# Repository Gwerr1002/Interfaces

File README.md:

## Interfases Programables

Proyectos del curso de Interfases Programables en lenguaje Micropython (ESP32).

## Temas
- Programación orientada a objetos y Estructuras de datos.
- Comunicación serie
- Interrupciones
- Eventos asíncronos
- Comunicación i2C y SPI
  - Acelerómetro MPU6050
  - Oxímetro MAX30102
  - Pantalla OLED SSD1306
- Comunicación Bluetooth
- IoT

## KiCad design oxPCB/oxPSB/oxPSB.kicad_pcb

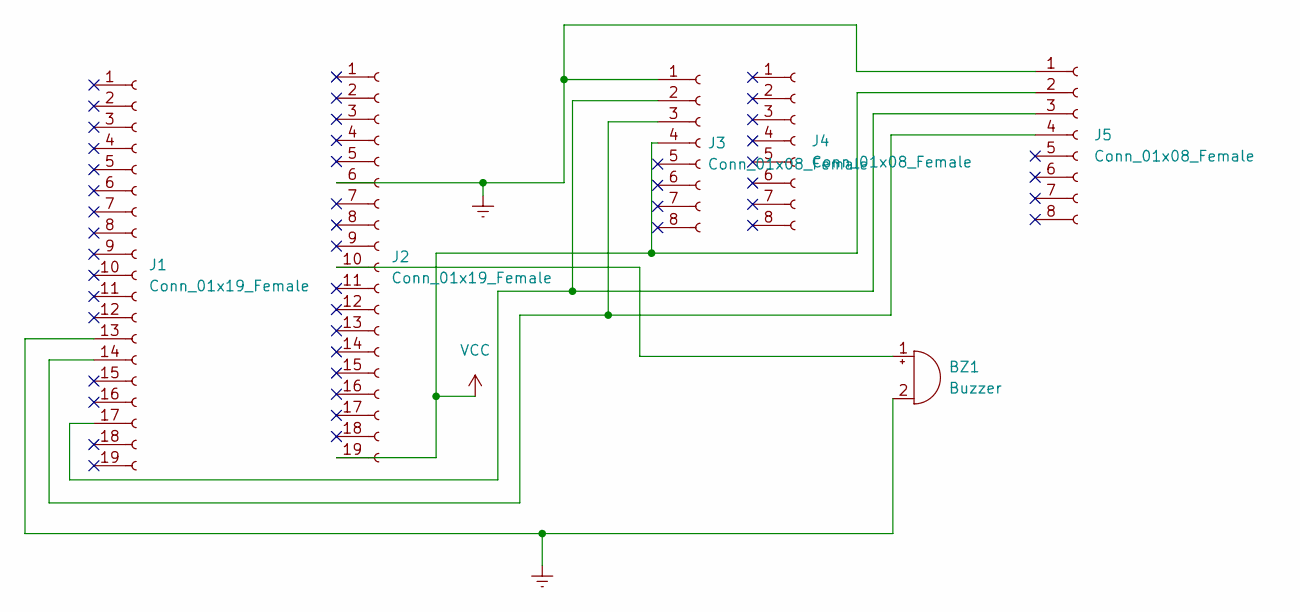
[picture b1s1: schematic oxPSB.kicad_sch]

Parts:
BZ1: Buzzer
J1: Conn_01x19_Female
J2: Conn_01x19_Female; PinHeader_1x19_P2.54mm_Vertical
J3, J5: Conn_01x08_Female; PinHeader_1x08_P2.54mm_Vertical
J4: Conn_01x08_Female

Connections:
Earth: BZ1.2 (+), J1.13, J2.6, J3.1, J5.1
unnamed: BZ1.1 (-), J2.10
unnamed: J1.14, J3.3, J5.4
unnamed: J1.17, J3.2, J5.3
VCC: J2.19, J3.4, J5.2

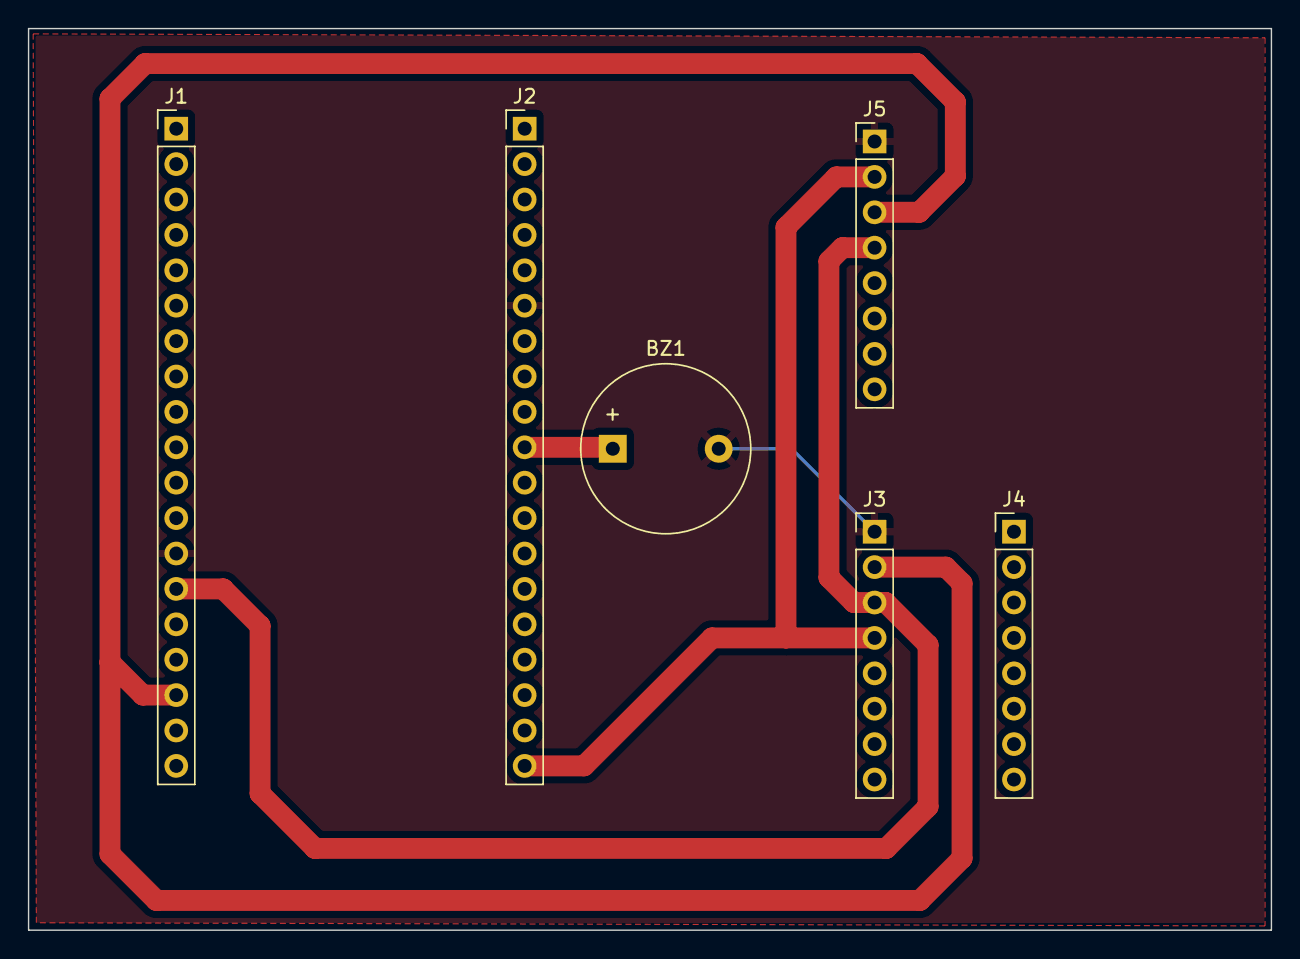
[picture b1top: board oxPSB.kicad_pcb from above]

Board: 2 copper layers, 89.2 x 64.7 mm, 6 parts (0 on the bottom side), 5 nets.

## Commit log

2022-10-26 Primer script que imprime hola mundo, tambien se incluyen comandos de git
2022-10-26 Se agrogó solo un espacio al print de hola mundo
2022-10-26 Agregue un monitor serial desarrollado en python como ejercicio de uso de git
2022-10-26 Volví a hacer commit ya que me equivoque en el proceso anterior
2022-10-27 Hoy vimos programación orientada a objetos
2022-11-08 Agregué ejemplos con micropython y comencè la nueva tarea
2022-11-08 Hice la tarea del 7 segmentos
    Aún requiere cambios
2022-11-09 Terminé de crear la tarea del 7 segmentos
2022-11-16 Avances con sensor y display Descargue las librerias para el manejo del sensor y del display OLED, tambièn hice algunas pruebas para verificar su funcionamiento
2022-11-16 Programa sensor + ssd OLED
    Hice un programa que lee del sensor MAX30102 y muestra el resultado en el display OLED
2022-11-16 prueba sensor + oled
    Hice algunas otras pruebas con el método get sirve, pero no entiendo aún su funcionamiento, ya que en algún punto da error con: no existe clear()
2022-11-17 Ejemplo de uso del sensor Encontre un nuevo ejemplo de uso del sensor, y grafiqué los datos obtenidos desde un archivo de texto
2022-11-18 Medición de lpm
    Hice un intento de medir la frecuencia cardiaca con una pila, tomo uno de cada 10 muestras y veo si existen máximos locales con una pila de tamaño 3. Aún no está en funcionamiento, no se logró medir.
2022-11-21 Avance con medición de frecuencia
    Mejoré la medición de la frecuencia con la pila. La pila remuestrea los datos y toma una muestra cada 20 datos, estima en qué punto hay un máximo y un mínimo. Guarda el valor máximo y mínimo y mide t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
2022-11-28 Complete el proyecto del oxímetro
    Esta vez hice el uso de tareas, en total sólo usé dos una para la adquisición, muestra de datos y la otra para la actualización de la temperatura.
2022-11-28 Añadí algunas modificaciones al oximetro
    Principalmente fueron de la pantalla OLED, para la actualización de los datos, como se interpolaban, la aproximación fue muy estrecha y tenía cierta cuadratura
2022-11-29 agregué lo de la clase pasada
2022-11-29 Hice los cambios finales que me pidio Omar en clase Solo combiè la forma en que se muestran los datos en pantalla como antes se hacìa sòlo que con vline
2022-11-29 Confirmar cambios anteriores Debido a que me saliò un aviso. Sòlo para estar seguros
2022-12-05 Agregué el diseño de la placa
    Para la práctica de la placa fenólica
2022-12-06 inicio interrupciones Vimos un ejemplo de como usar unas interrupciones
2022-12-06 Tarea interrupciones GPIO
    Omar nos pidió sólo encender un led cuando presionáramos un botón y apagarlo cuando dejáramos de presionarlo
2022-12-07 bluetooth Hoy vimos bluetooth e intentè usar la librería de pyblue
2022-12-13 ble movi a mi carpeta el archivo ble del ejemplo de uso del bluetooth
2022-12-19 IoT
    Hice la tarea de IoT que es conectar con alguna aplicación, en mi caso usé gmail para enviar correos
2022-12-20 IMU encontrè un código para el control del IMU
2022-12-20 Comienzo del proyecto final
    Comencé el proyecto final intentando mezclar la lectura del IMU con el envío bluetooth
2022-12-20 up
    actual
2022-12-21 uso de bleak y actualización ESP32
    Actualicé los programas de recepción de datos bluetooth de la esp y compu
2022-12-24 Bluetooth ESP'S
    Logré comunicarme con dos ESP32 a la vez
2022-12-24 ESP32
    Actualización de la esp32 solo eliminé algunas líneas innecesarias
2022-12-31 Agregue algunos ejemplos de graficacion con animación
2023-01-08 Avances Con la adquisición de dos dispositivos y la gráfica en tiempo real pero esta aún no está disponible.
2023-01-09 Avance grafica
    Avance con la grafica en tiempo real
2023-01-10 caida inicio
    Desarrollo del cambio de proyecto a detección de caida
2023-01-10 avances caida
    Hice algunos analisis estadisticos con diagramas de caja (quantiles) y comence el algoritmo para la deteccion de caida
2023-01-11 Termino del proyecto caida
    Termine de realizar el proyecto de caida
    Please enter the commit message for your changes. Lines starting
